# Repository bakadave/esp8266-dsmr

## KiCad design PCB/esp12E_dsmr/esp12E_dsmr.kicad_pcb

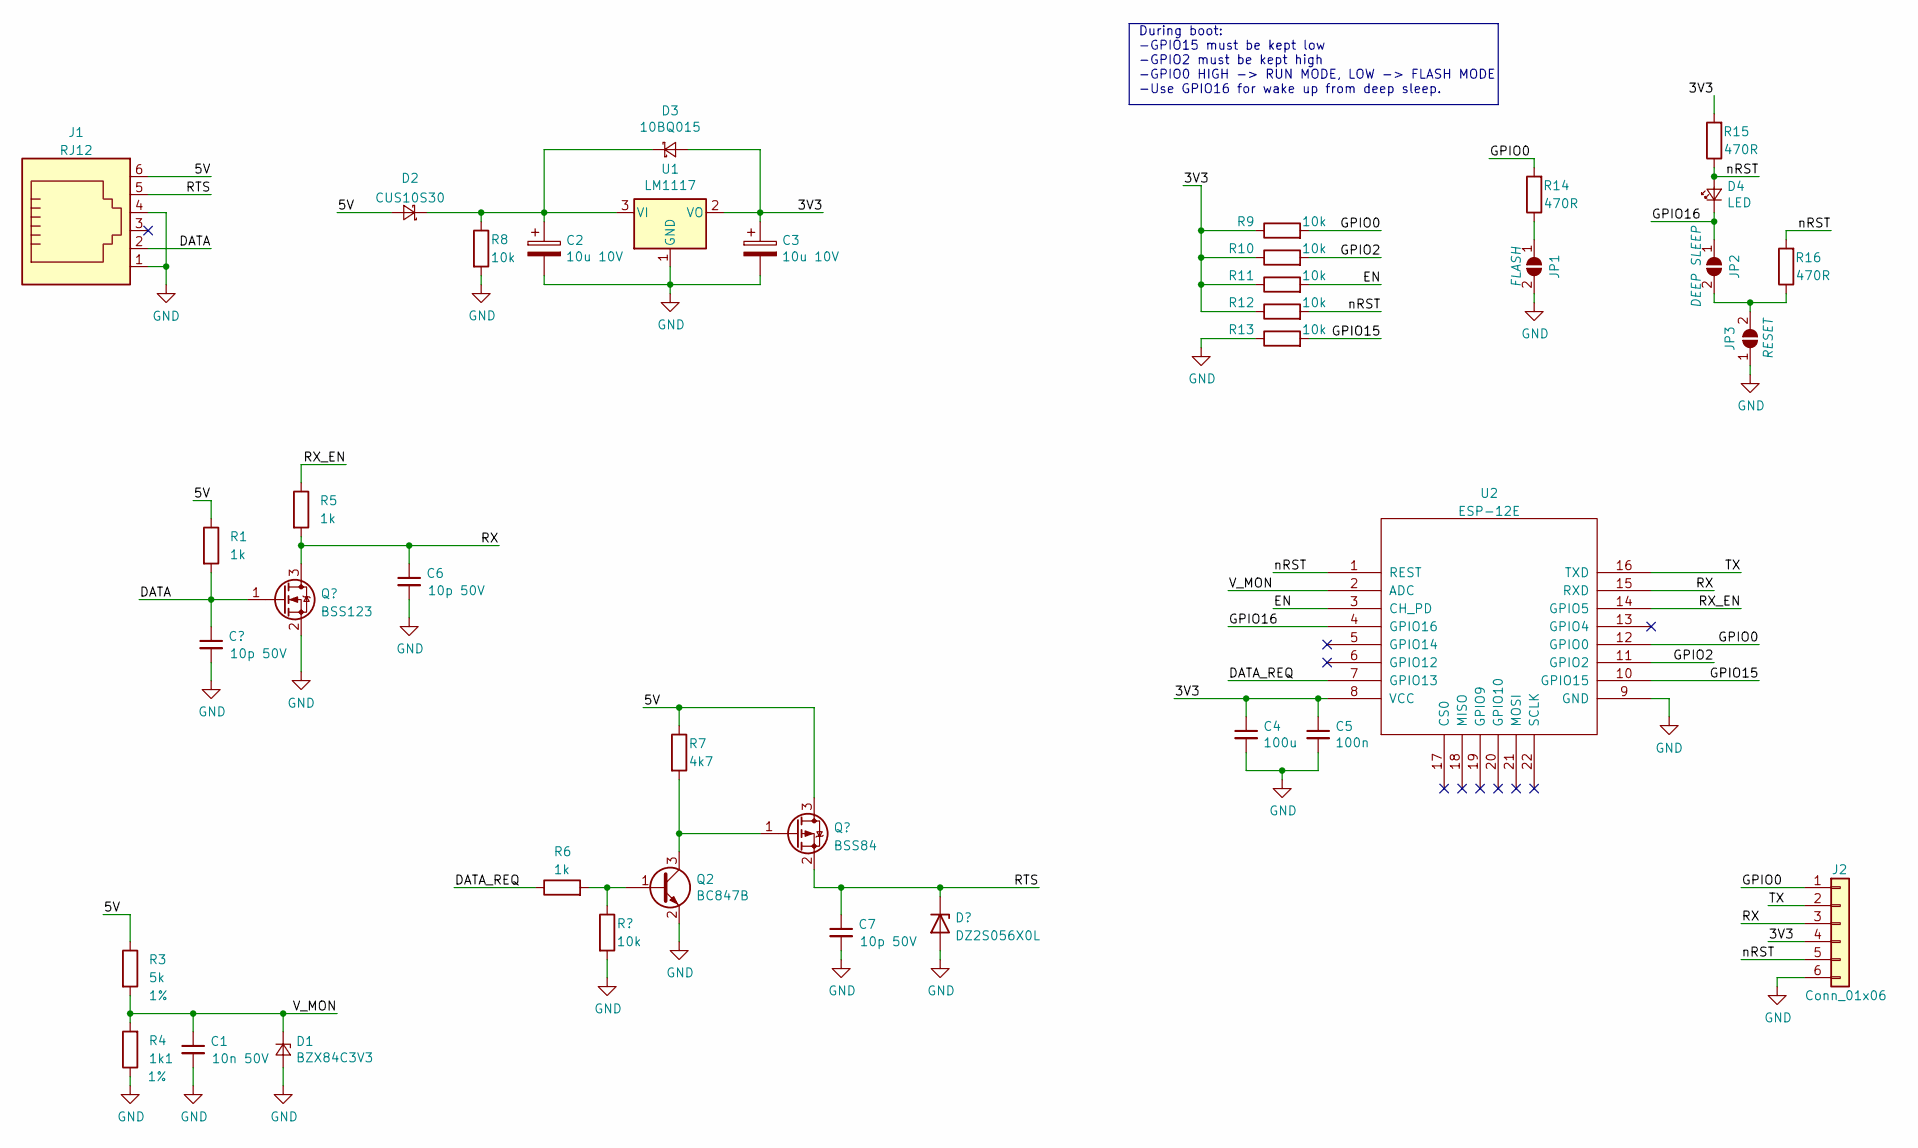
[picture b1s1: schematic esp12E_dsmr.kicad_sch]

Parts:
C1: 10n 50V; CAP_0805; MPN CC0805JKNPO9BN103; LCSC C527201
C2, C3: 10u 10V; CP_EIA-3216-18_Kemet-A_Pad1.58x1.35mm_HandSolder; MPN T529P106M010AAE200; LCSC C696821
C4: 100u; C_1206_3216Metric; MPN CC1206MKX5R5BB107; LCSC C110048
C5: 100n; CAP_0805; MPN CC0805KRX7R9BB104; LCSC C49678
C6, C7: 10p 50V; CAP_0805; MPN CC0805JRNPOABN100; LCSC C576965
D1: BZX84C3V3; D_SOT-23_ANK; MPN BZX84C3V3LT1G; LCSC C82473
D2: CUS10S30; D_SOD-323_HandSoldering; MPN CUS10S30,H3F; LCSC C146335
D3: 10BQ015; D_SMB; MPN VS-10BQ015-M3/5BT; LCSC C413466
D4: LED; LED_0805; MPN 17-215/BHC-AP1Q2/3T; LCSC C131208
J1: RJ12; RJ25_Wayconn_MJEA-660X1_Horizontal
J2: Conn_01x06; PinHeader_1x06_P2.54mm_Vertical
JP1, JP2, JP3: SolderJumper_2_Open; SolderJumper-2_P1.3mm_Open_TrianglePad1.0x1.5mm
Q2: BC847B; SOT-23; MPN BC847BLT1G; LCSC C94393
R1, R5, R6: 1k; RES_0805; MPN RC0805JR-071KL; LCSC C100046
R3: 5k; RES_0805
R4: 1k1; RES_0805
R7: 4k7; RES_0805
R8, R9, R10, R11, R12, R13: 10k; RES_0805; MPN RC0805JR-0710KL; LCSC C100047
R14, R15, R16: 470R; RES_0805; MPN RC0805JR-07470RL; LCSC C114747
U1: LM1117; SOT-223-3_TabPin2; MPN LM1117IMPX-3.3/NOPB; LCSC C23984
U2: ESP-12E

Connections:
/3V3: C3.1, C4.1, C5.1, D3.2 (A), J2.4, R9.1, R10.1, R11.1, R12.1, R15.2, U1.2 (VO), U2.8 (VCC)
/5V: D2.2 (A), J1.6, R1.1, R3.1, R7.1; also elsewhere on the board
/DATA: J1.2, R1.2; also elsewhere on the board
/DATA_REQ: R6.1, U2.7 (GPIO13)
/EN: R11.2, U2.3 (CH_PD)
/GPIO0: J2.1, R9.2, R14.2, U2.12 (GPIO0)
/GPIO2: R10.2, U2.11 (GPIO2)
/GPIO15: R13.2, U2.10 (GPIO15)
/GPIO16: D4.1 (K), JP2.1 (A), U2.4 (GPIO16)
/RTS: C7.1, J1.5; also elsewhere on the board
/RX: C6.1, J2.3, R5.2, U2.15 (RXD); also elsewhere on the board
/RX_EN: R5.1, U2.14 (GPIO5)
/TX: J2.2, U2.16 (TXD)
/V_MON: C1.1, D1.1 (K), R3.2, R4.2, U2.2 (ADC)
/nRST: D4.2 (A), J2.5, R12.2, R15.1, R16.2, U2.1 (REST)
GND: C1.2, C2.2, C3.2, C4.2, C5.2, C6.2, C7.2, D1.2 (A), J1.1, J1.4, J2.6, JP1.2 (B), JP3.1 (A), Q2.2 (E), R4.1, R8.2, R13.1, U1.1 (GND), U2.9 (GND); also elsewhere on the board
unnamed: C2.1, D2.1 (K), D3.1 (K), R8.1, U1.3 (VI)
unnamed: JP1.1 (A), R14.1
unnamed: JP2.2 (B), JP3.2 (B), R16.1
unnamed: Q2.1 (B), R6.2
unnamed 21: Q2.3 (C), R7.2; also elsewhere on the board

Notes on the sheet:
During boot: -GPIO15 must be kept low -GPIO2 must be kept high -GPIO0 HIGH -> RUN MODE, LOW -> FLASH MODE -Use GPIO16 for wake up from deep sleep.

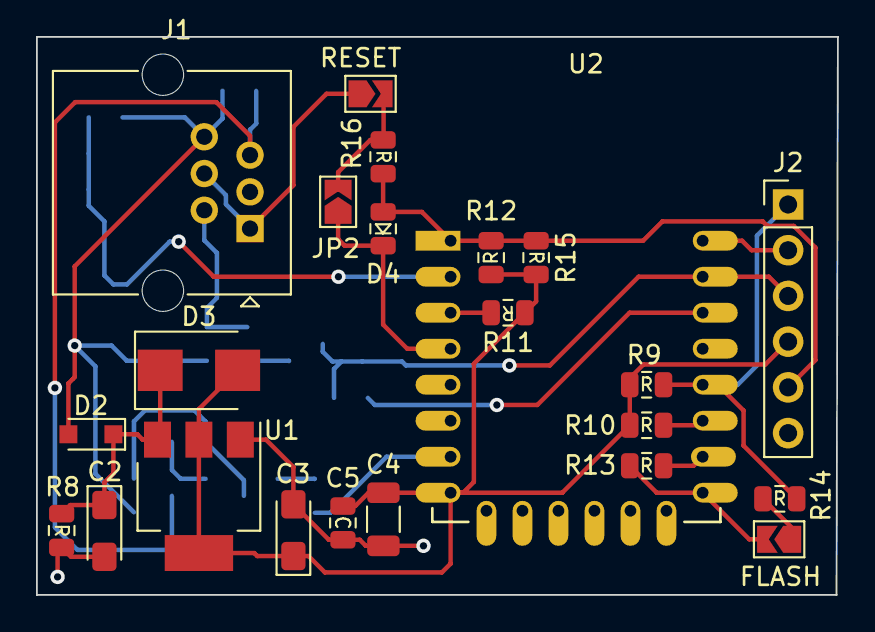
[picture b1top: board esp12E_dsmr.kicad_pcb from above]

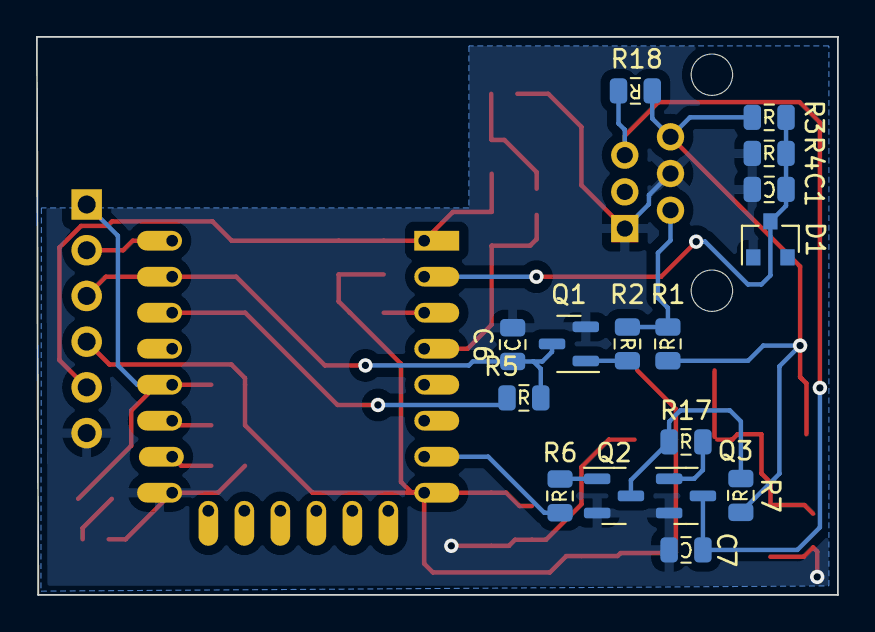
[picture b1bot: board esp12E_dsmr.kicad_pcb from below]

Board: 2 copper layers, 44.5 x 31.0 mm, 39 parts (16 on the bottom side), 23 nets.

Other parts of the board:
Q1, Q3: BC847B; SOT-23
R2, R17: 2k2; RES_0805
R18: 10k; RES_0805

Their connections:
/5V: R18.1; also elsewhere on the board
/DATA: R2.1; also elsewhere on the board
/RTS: Q3.3 (C), R18.2; also elsewhere on the board
/RX: Q1.3 (C); also elsewhere on the board
GND: Q1.2 (E), Q3.2 (E); also elsewhere on the board
unnamed: Q1.1 (B), R2.2
unnamed 21: R17.1; also elsewhere on the board
unnamed: Q3.1 (B), R17.2

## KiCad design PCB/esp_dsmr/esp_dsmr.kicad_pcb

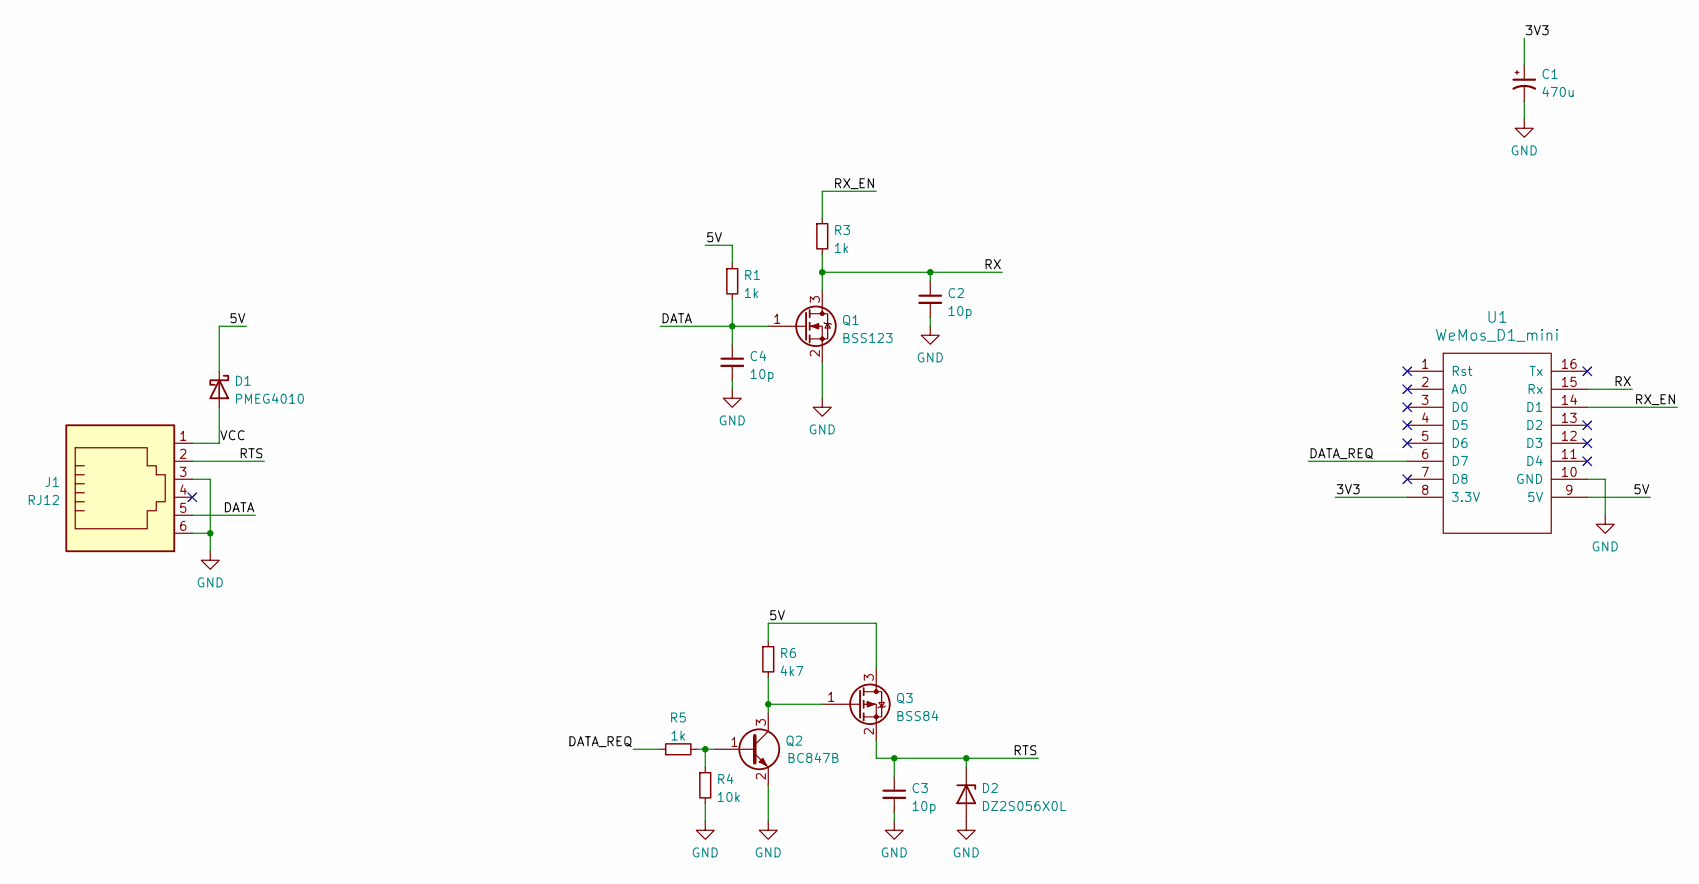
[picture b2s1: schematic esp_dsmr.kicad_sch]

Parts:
C1: 470u; C_Radial_D8.0mm_H11.5mm_P3.50mm
C2, C3, C4: 10p; CAP_0805
D1: PMEG4010; D_SOD-128; MPN PMEG4010EP,115
D2: DZ2S056X0L; D_SOD-523
J1: RJ12; RJ25_Wayconn_MJEA-660X1_Horizontal
Q1: BSS123; SOT-23
Q2: BC847B; SOT-23; MPN BC847BLT1G; LCSC C94393
Q3: BSS84; SOT-23
R1, R3, R5: 1k; RES_0805
R4: 10k; RES_0805
R6: 4k7; RES_0805
U1: WeMos_D1_mini; WEMOS_D1_mini_light

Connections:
/3V3: C1.1, U1.8 (3.3V)
/5V: D1.1 (K), Q3.3 (D), R1.1, R6.1, U1.9 (5V)
/DATA: C4.1, J1.5, Q1.1 (G), R1.2
/DATA_REQ: R5.1, U1.6 (D7)
/RTS: C3.1, D2.1 (K), J1.2, Q3.2 (S)
/RX: C2.1, Q1.3 (D), R3.2, U1.15 (Rx)
/RX_EN: R3.1, U1.14 (D1)
/VCC: D1.2 (A), J1.1
GND: C1.2, C2.2, C3.2, C4.2, D2.2 (A), J1.3, J1.6, Q1.2 (S), Q2.2 (E), R4.2, U1.10 (GND)
unnamed: Q2.1 (B), R4.1, R5.2
unnamed: Q2.3 (C), Q3.1 (G), R6.2

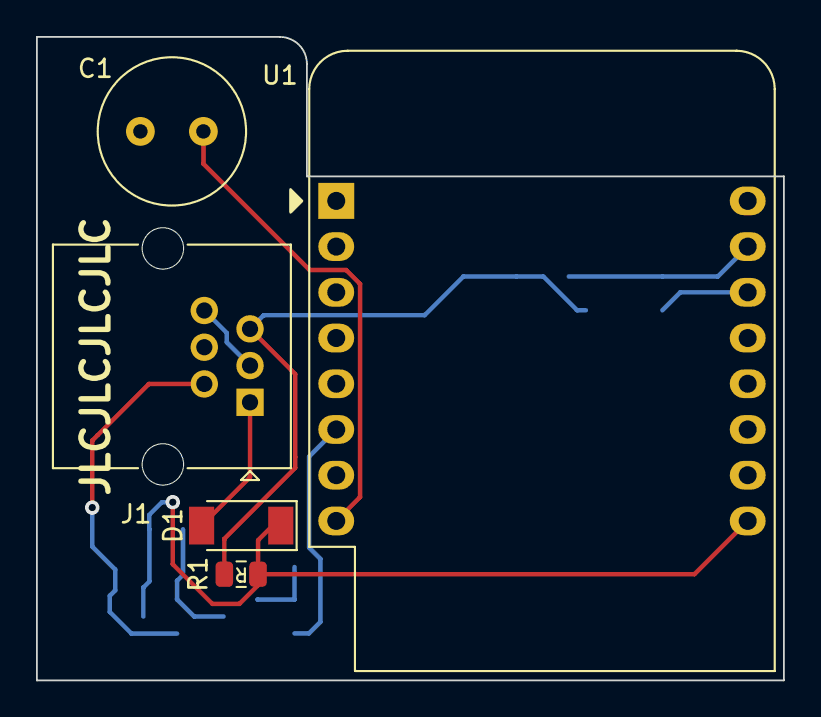
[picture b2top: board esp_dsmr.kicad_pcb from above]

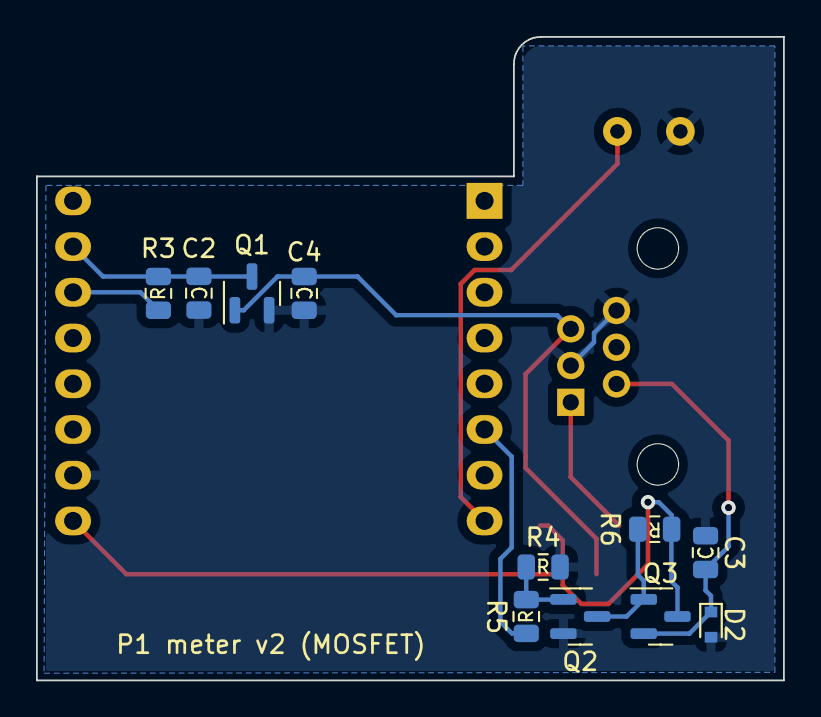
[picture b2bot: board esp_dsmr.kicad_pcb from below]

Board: 2 copper layers, 41.5 x 35.8 mm, 16 parts (11 on the bottom side), 11 nets.

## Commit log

2023-01-03 refactor and PCB
